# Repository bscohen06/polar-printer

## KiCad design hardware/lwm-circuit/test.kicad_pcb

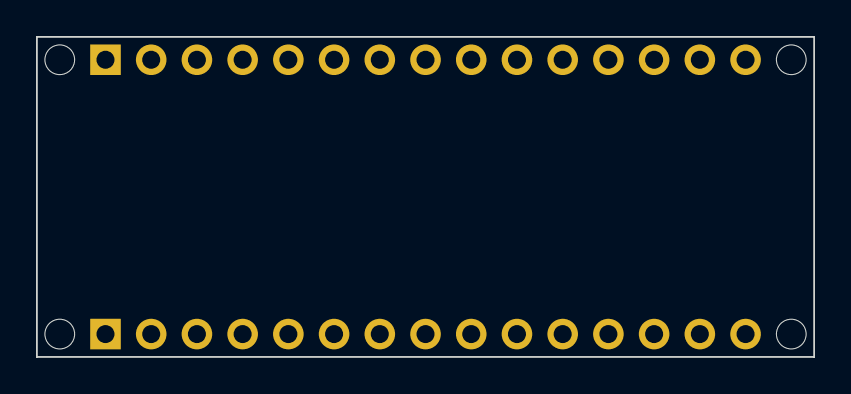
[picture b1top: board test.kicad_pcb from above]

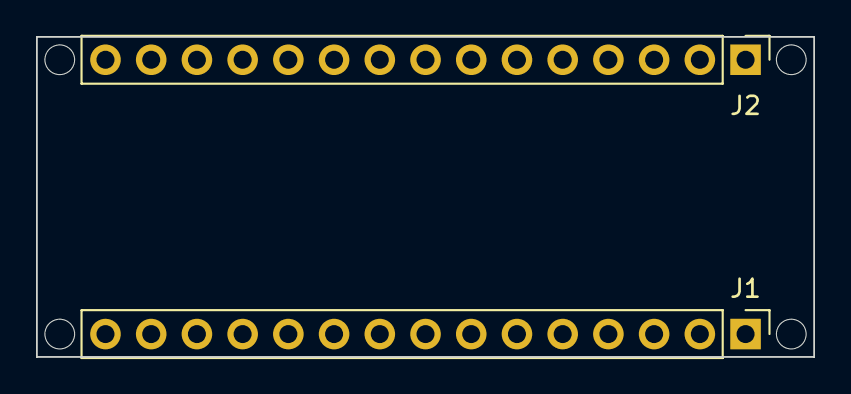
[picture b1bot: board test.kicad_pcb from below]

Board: 2 copper layers, 43.2 x 17.8 mm, 6 parts (2 on the bottom side), 2 nets, no tracks yet.

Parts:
J1: Analog; PinHeader_1x15_P2.54mm_Vertical
J2: Digital; PinHeader_1x15_P2.54mm_Vertical
MH1, MH2, MH3, MH4: MountingHole_65mil

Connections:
/~RESET: J1.13, J2.13
GND: J1.14, J2.12

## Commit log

2026-06-01 Early circuit design
2026-06-07 Added SD card reader,
2026-06-07 Added more labels
2026-06-07 Updated files
2026-06-07 removed unnessary stepper motors
2026-06-07 wired sd card
2026-06-07 Added full labels to drivers
2026-06-07 rewired sd card
2026-06-07 added ultrasonic sensors
2026-06-07 Added base plate driver
